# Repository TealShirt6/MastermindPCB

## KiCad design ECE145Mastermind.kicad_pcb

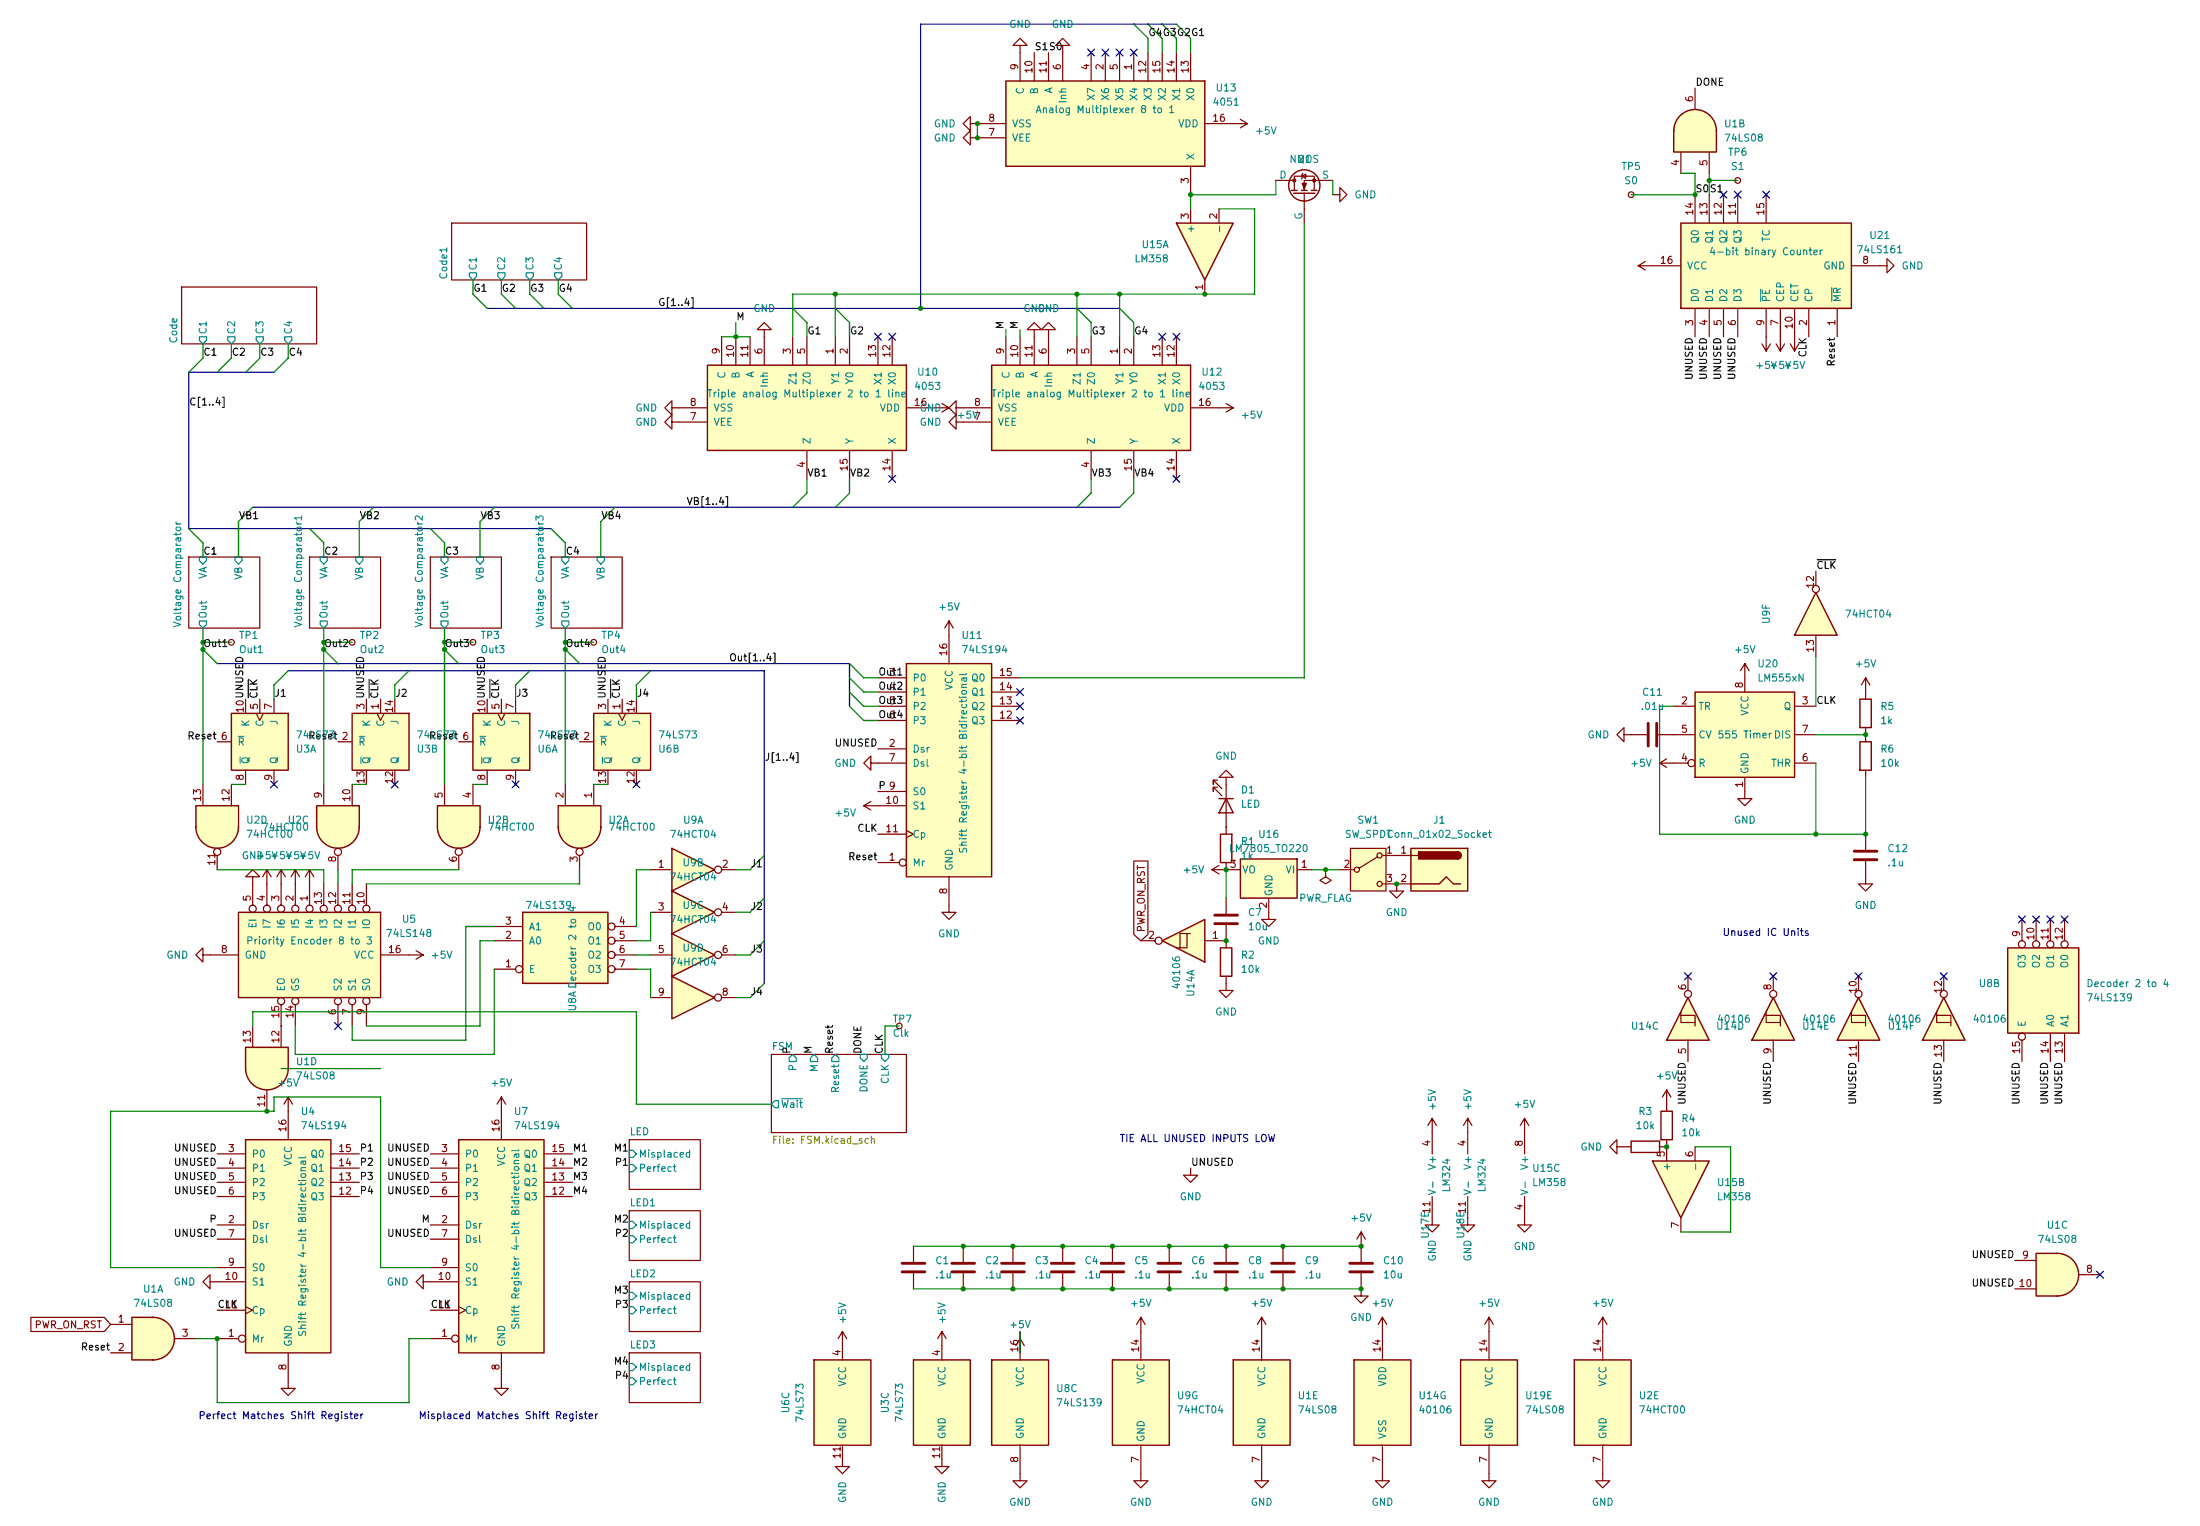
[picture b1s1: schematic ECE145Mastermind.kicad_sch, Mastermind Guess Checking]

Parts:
C1, C2, C3, C4, C5, C6, C8, C9, C12: .1u; C_0805_2012Metric_Pad1.18x1.45mm_HandSolder
C7, C10: 10u; C_0805_2012Metric_Pad1.18x1.45mm_HandSolder
C11: .01u; C_0805_2012Metric_Pad1.18x1.45mm_HandSolder
D1: LED; LED_0805_2012Metric_Pad1.15x1.40mm_HandSolder
J1: Conn_01x02_Socket; BarrelJack_Horizontal
Q1: NMOS; TO-220-3_Horizontal_TabDown
R1, R5: 1k; R_0805_2012Metric_Pad1.20x1.40mm_HandSolder
R2, R3, R4, R6: 10k; R_0805_2012Metric_Pad1.20x1.40mm_HandSolder
SW1: SW_SPDT; SW_Slide_SPDT_Straight_CK_OS102011MS2Q
TP1: Out1; TestPoint_Pad_1.5x1.5mm
TP2: Out2; TestPoint_Pad_1.5x1.5mm
TP3: Out3; TestPoint_Pad_1.5x1.5mm
TP4: Out4; TestPoint_Pad_1.5x1.5mm
TP5: S0; TestPoint_Pad_1.5x1.5mm
TP6: S1; TestPoint_Pad_1.5x1.5mm
TP7: Clk; TestPoint_Pad_1.5x1.5mm
U1, U19: 74LS08; SOIC-14_3.9x8.7mm_P1.27mm
U2: 74HCT00; SOIC-14_3.9x8.7mm_P1.27mm
U3, U6: 74LS73; SOIC-14_3.9x8.7mm_P1.27mm
U4, U7, U11: 74LS194; SOIC-16_3.9x9.9mm_P1.27mm
U5: 74LS148; SOIC-16_3.9x9.9mm_P1.27mm
U8: 74LS139; SOIC-16_3.9x9.9mm_P1.27mm
U9: 74HCT04; SOIC-14_3.9x8.7mm_P1.27mm
U10, U12: 4053; SOIC-16_3.9x9.9mm_P1.27mm
U13: 4051; SOIC-16_3.9x9.9mm_P1.27mm
U14: 40106; SOIC-14_3.9x8.7mm_P1.27mm
U15: LM358; SOIC-8_3.9x4.9mm_P1.27mm
U16: LM7805_TO220; TO-220-3_Horizontal_TabDown
U17, U18: LM324; SOIC-14_3.9x8.7mm_P1.27mm
U20: LM555xN; SOIC-8_3.9x4.9mm_P1.27mm
U21: 74LS161; SOIC-16_3.9x9.9mm_P1.27mm

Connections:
+5V: C1.1, C2.1, C3.1, C4.1, C5.1, C6.1, C7.1, C8.1, C9.1, C10.1, R1.1, R4.1, R5.1, U1.14 (VCC), U2.14 (VCC), U3.4 (VCC), U4.16 (VCC), U5.1 (I4), U5.2 (I5), U5.3 (I6), U5.4 (I7), U5.16 (VCC), U6.4 (VCC), U7.16 (VCC), U8.16 (VCC), U9.14 (VCC), U10.16 (VDD), U11.10 (S1), U11.16 (VCC), U12.16 (VDD), U13.16 (VDD), U14.14 (VDD), U15.8 (V+), U16.3 (VO), U17.4 (V+), U18.4 (V+), U19.14 (VCC), U20.4 (R), U20.8 (VCC), U21.7 (CEP), U21.9 (~PE), U21.10 (CET), U21.16 (VCC); also elsewhere on the board
/CLK: TP7.1 (1_1), U4.11 (Cp), U7.11 (Cp), U9.13, U11.11 (Cp), U20.3 (Q), U21.2 (CP); also elsewhere on the board
/DONE: U1.6; also elsewhere on the board
/FSM/~Wait: U1.13; also elsewhere on the board
/G1: U10.5 (Z0), U13.13 (X0); also elsewhere on the board
/G2: U10.2 (Y0), U13.14 (X1); also elsewhere on the board
/G3: U12.5 (Z0), U13.15 (X2); also elsewhere on the board
/G4: U12.2 (Y0), U13.12 (X3); also elsewhere on the board
/J1: U3.7 (J), U9.2
/J2: U3.14 (J), U9.4
/J3: U6.7 (J), U9.6
/J4: U6.14 (J), U9.8
/M: U7.2 (Dsr), U10.9 (C), U10.10 (B), U10.11 (A), U12.9 (C), U12.10 (B); also elsewhere on the board
/M1: U7.15 (Q0); also elsewhere on the board
/M2: U7.14 (Q1); also elsewhere on the board
/M3: U7.13 (Q2); also elsewhere on the board
/M4: U7.12 (Q3); also elsewhere on the board
/Out1: TP1.1 (1_1), U2.13, U11.3 (P0); also elsewhere on the board
/Out2: TP2.1 (1_1), U2.9, U11.4 (P1); also elsewhere on the board
/Out3: TP3.1 (1_1), U2.5, U11.5 (P2); also elsewhere on the board
/Out4: TP4.1 (1_1), U2.2, U11.6 (P3); also elsewhere on the board
/P: U4.2 (Dsr), U11.9 (S0); also elsewhere on the board
/P1: U4.15 (Q0); also elsewhere on the board
/P2: U4.14 (Q1); also elsewhere on the board
/P3: U4.13 (Q2); also elsewhere on the board
/P4: U4.12 (Q3); also elsewhere on the board
/Reset: U1.2, U3.2 (~R), U3.6 (~R), U6.2 (~R), U6.6 (~R), U11.1 (Mr), U21.1 (~MR); also elsewhere on the board
/S0: TP5.1 (1_1), U1.4, U13.11 (A), U21.14 (Q0)
/S1: TP6.1 (1_1), U1.5, U13.10 (B), U21.13 (Q1)
/VB1: U10.4 (Z); also elsewhere on the board
/VB2: U10.15 (Y); also elsewhere on the board
/VB3: U12.4 (Z); also elsewhere on the board
/VB4: U12.15 (Y); also elsewhere on the board
/~CLK: U3.1 (C), U3.5 (C), U6.1 (C), U6.5 (C), U9.12
GND: C1.2, C2.2, C3.2, C4.2, C5.2, C6.2, C8.2, C9.2, C10.2, C11.2, C12.2, D1.1 (K), J1.2, Q1.3 (S), R2.2, R3.1, SW1.3 (C), U1.7 (GND), U1.9, U1.10, U2.7 (GND), U3.3 (K), U3.10 (K), U3.11 (GND), U4.3 (P0), U4.4 (P1), U4.5 (P2), U4.6 (P3), U4.7 (Dsl), U4.8 (GND), U4.10 (S1), U5.5 (EI), U5.8 (GND), U6.3 (K), U6.10 (K), U6.11 (GND), U7.3 (P0), U7.4 (P1), U7.5 (P2), U7.6 (P3), U7.7 (Dsl), U7.8 (GND), U7.10 (S1), U8.8 (GND), U8.13 (A1), U8.14 (A0), U8.15 (E), U9.7 (GND), U10.6 (Inh), U10.7 (VEE), U10.8 (VSS), U11.2 (Dsr), U11.7 (Dsl), U11.8 (GND), U12.6 (Inh), U12.7 (VEE), U12.8 (VSS), U12.11 (A), U13.6 (Inh), U13.7 (VEE), U13.8 (VSS), U13.9 (C), U14.5, U14.7 (VSS), U14.9, U14.11, U14.13, U15.4 (V-), U16.2 (GND), U17.11 (V-), U18.11 (V-), U19.7 (GND), U20.1 (GND), U21.3 (D0), U21.4 (D1), U21.5 (D2), U21.6 (D3), U21.8 (GND); also elsewhere on the board
unnamed: C7.2, R2.1, U14.1
unnamed: D1.2 (A), R1.2
unnamed: Q1.2 (D), U13.3 (X), U15.3 (+)
unnamed: Q1.1 (G), U11.15 (Q0)
unnamed: J1.1, SW1.1 (A)
unnamed: SW1.2 (B), U16.1 (VI)
unnamed: U2.12, U3.8 (~Q)
unnamed: U2.10, U3.13 (~Q)
unnamed: U1.3, U4.1 (Mr), U7.1 (Mr)
unnamed: U1.11, U4.9 (S0), U7.9 (S0)
unnamed: U1.12, U5.15 (EO)
unnamed: U5.14 (GS), U8.1 (E)
unnamed: U2.6, U5.11 (I1)
unnamed: U2.8, U5.12 (I2)
unnamed: U2.11, U5.13 (I3)
unnamed: U2.3, U5.10 (IO)
unnamed: U5.9 (S0), U8.2 (A0)
unnamed: U5.7 (S1), U8.3 (A1)
unnamed: U2.4, U6.8 (~Q)
unnamed: U2.1, U6.13 (~Q)
unnamed: U8.4 (O0), U9.1
unnamed: U8.5 (O1), U9.3
unnamed: U8.6 (O2), U9.5
unnamed: U8.7 (O3), U9.9
unnamed: U10.1 (Y1), U10.3 (Z1), U12.1 (Y1), U12.3 (Z1), U15.1, U15.2 (-)
unnamed: R3.2, R4.2, U15.5 (+)
unnamed: U15.6 (-), U15.7
unnamed: C11.1, U20.5 (CV)
unnamed: R5.2, R6.1, U20.7 (DIS)
unnamed: C12.1, R6.2, U20.2 (TR), U20.6 (THR)
PWR_ON_RST: U1.1, U14.2; also elsewhere on the board

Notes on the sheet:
Misplaced Matches Shift Register
Perfect Matches Shift Register
Unused IC Units
TIE ALL UNUSED INPUTS LOW

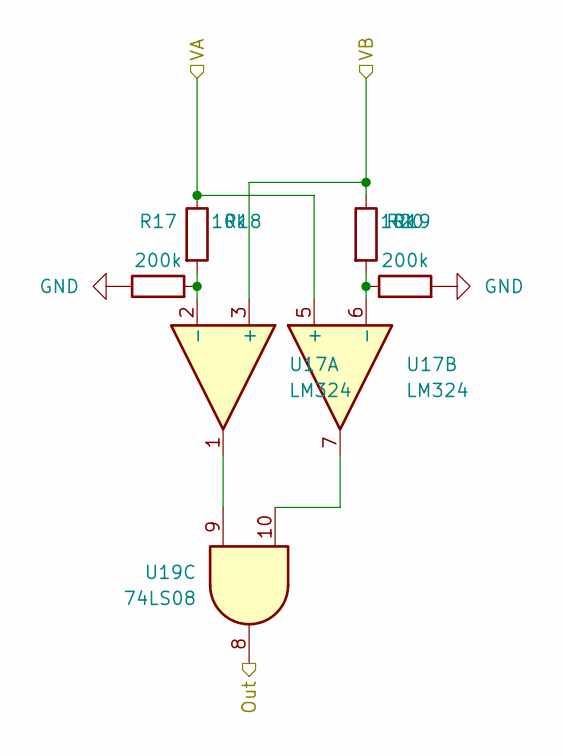
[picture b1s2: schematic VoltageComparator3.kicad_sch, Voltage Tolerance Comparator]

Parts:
R17, R20: 200k; R_0805_2012Metric_Pad1.20x1.40mm_HandSolder
R18, R19: 10k; R_0805_2012Metric_Pad1.20x1.40mm_HandSolder
U17: LM324; SOIC-14_3.9x8.7mm_P1.27mm
U19: 74LS08; SOIC-14_3.9x8.7mm_P1.27mm

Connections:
/C3: R18.1, U17.5 (+); also elsewhere on the board
/Out3: U19.8; also elsewhere on the board
/VB3: R19.1, U17.3 (+); also elsewhere on the board
GND: R17.1, R20.2; also elsewhere on the board
unnamed: U17.1, U19.9
unnamed: U17.7, U19.10
unnamed: R17.2, R18.2, U17.2 (-)
unnamed: R19.2, R20.1, U17.6 (-)

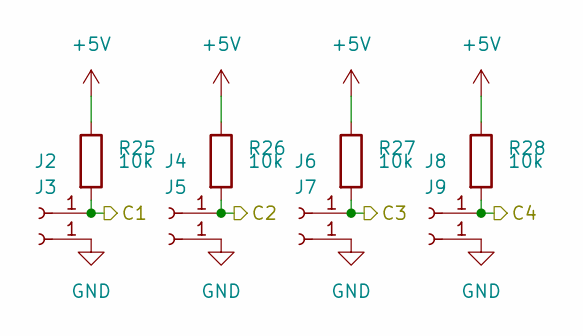
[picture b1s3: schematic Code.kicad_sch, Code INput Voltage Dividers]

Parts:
J2, J3, J4, J5, J6, J7, J8, J9: Conn_01x01_Socket; PinSocket_1x01_P2.54mm_Vertical
R25, R26, R27, R28: 10k; R_0805_2012Metric_Pad1.20x1.40mm_HandSolder

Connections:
+5V: R25.1, R26.1, R27.1, R28.1; also elsewhere on the board
/C1: J2.1 (Pin_1_1), R25.2; also elsewhere on the board
/C2: J4.1 (Pin_1_1), R26.2; also elsewhere on the board
/C3: J6.1 (Pin_1_1), R27.2; also elsewhere on the board
/C4: J8.1 (Pin_1_1), R28.2; also elsewhere on the board
GND: J3.1 (Pin_1_1), J5.1 (Pin_1_1), J7.1 (Pin_1_1), J9.1 (Pin_1_1); also elsewhere on the board

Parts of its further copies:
J10, J11, J12, J13, J14, J15, J16, J17: Conn_01x01_Socket; PinSocket_1x01_P2.54mm_Vertical
R29, R30, R31, R32: 10k; R_0805_2012Metric_Pad1.20x1.40mm_HandSolder

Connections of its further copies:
+5V: R29.1, R30.1, R31.1, R32.1; also elsewhere on the board
/G1: J10.1 (Pin_1_1), R29.2; also elsewhere on the board
/G2: J12.1 (Pin_1_1), R30.2; also elsewhere on the board
/G3: J14.1 (Pin_1_1), R31.2; also elsewhere on the board
/G4: J16.1 (Pin_1_1), R32.2; also elsewhere on the board
GND: J11.1 (Pin_1_1), J13.1 (Pin_1_1), J15.1 (Pin_1_1), J17.1 (Pin_1_1); also elsewhere on the board

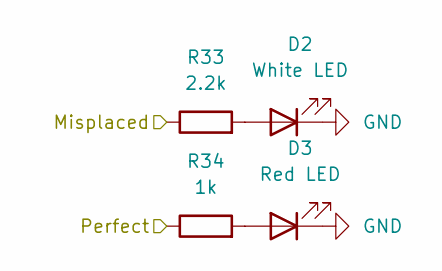
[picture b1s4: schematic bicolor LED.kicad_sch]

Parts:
D2: White LED; LED_0603_1608Metric_Pad1.05x0.95mm_HandSolder
D3: Red LED; LED_0603_1608Metric_Pad1.05x0.95mm_HandSolder
R33: 2.2k; R_0805_2012Metric_Pad1.20x1.40mm_HandSolder
R34: 1k; R_0805_2012Metric_Pad1.20x1.40mm_HandSolder

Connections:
/M2: R33.1; also elsewhere on the board
/P2: R34.1; also elsewhere on the board
GND: D2.1 (K), D3.1 (K); also elsewhere on the board
unnamed: D2.2 (A), R33.2
unnamed: D3.2 (A), R34.2

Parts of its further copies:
D4, D6, D8: White LED; LED_0603_1608Metric_Pad1.05x0.95mm_HandSolder
D5, D7, D9: Red LED; LED_0603_1608Metric_Pad1.05x0.95mm_HandSolder
R35, R37, R39: 2.2k; R_0805_2012Metric_Pad1.20x1.40mm_HandSolder
R36, R38, R40: 1k; R_0805_2012Metric_Pad1.20x1.40mm_HandSolder

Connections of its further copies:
/M1: R37.1; also elsewhere on the board
/M3: R35.1; also elsewhere on the board
/M4: R39.1; also elsewhere on the board
/P1: R38.1; also elsewhere on the board
/P3: R36.1; also elsewhere on the board
/P4: R40.1; also elsewhere on the board
GND: D4.1 (K), D5.1 (K), D6.1 (K), D7.1 (K), D8.1 (K), D9.1 (K); also elsewhere on the board
unnamed: D4.2 (A), R35.2
unnamed: D5.2 (A), R36.2
unnamed: D6.2 (A), R37.2
unnamed: D7.2 (A), R38.2
unnamed: D8.2 (A), R39.2
unnamed: D9.2 (A), R40.2

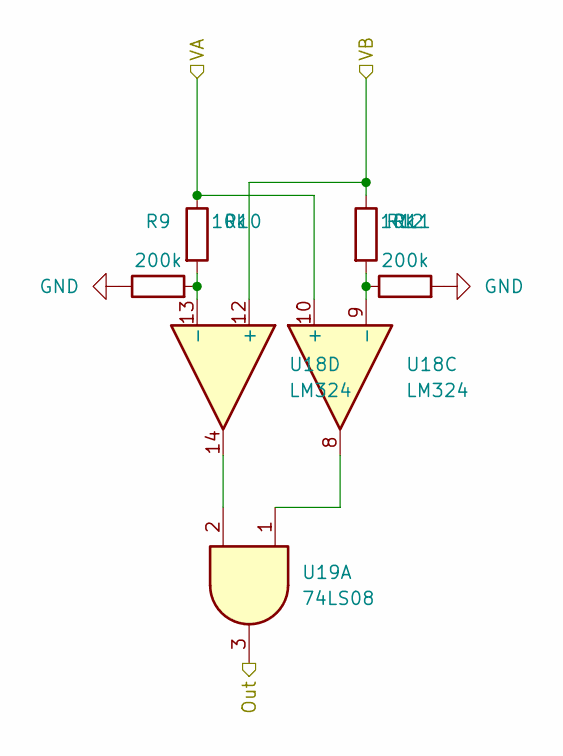
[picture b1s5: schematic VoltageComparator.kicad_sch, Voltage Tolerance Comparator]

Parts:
R9, R12: 200k; R_0805_2012Metric_Pad1.20x1.40mm_HandSolder
R10, R11: 10k; R_0805_2012Metric_Pad1.20x1.40mm_HandSolder
U18: LM324; SOIC-14_3.9x8.7mm_P1.27mm
U19: 74LS08; SOIC-14_3.9x8.7mm_P1.27mm

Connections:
/C1: R10.1, U18.10 (+); also elsewhere on the board
/Out1: U19.3; also elsewhere on the board
/VB1: R11.1, U18.12 (+); also elsewhere on the board
GND: R9.1, R12.2; also elsewhere on the board
unnamed: U18.8, U19.1
unnamed: U18.14, U19.2
unnamed: R11.2, R12.1, U18.9 (-)
unnamed: R9.2, R10.2, U18.13 (-)

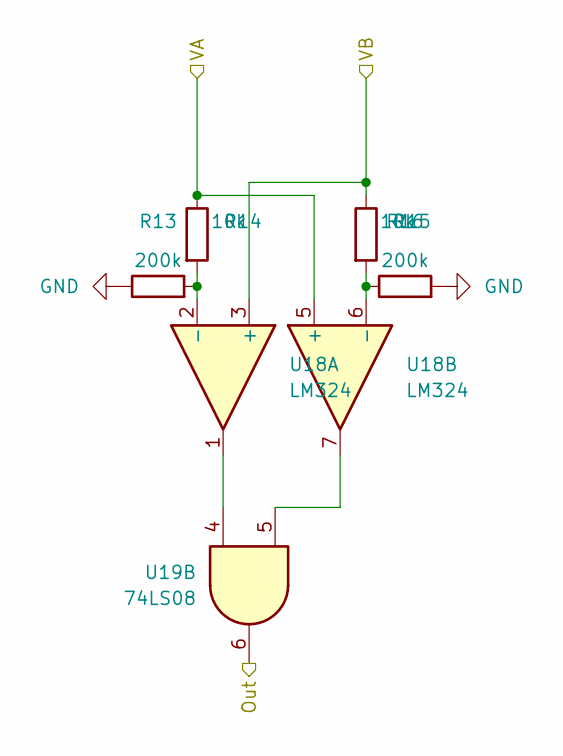
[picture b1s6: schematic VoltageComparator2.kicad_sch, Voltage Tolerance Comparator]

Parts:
R13, R16: 200k; R_0805_2012Metric_Pad1.20x1.40mm_HandSolder
R14, R15: 10k; R_0805_2012Metric_Pad1.20x1.40mm_HandSolder
U18: LM324; SOIC-14_3.9x8.7mm_P1.27mm
U19: 74LS08; SOIC-14_3.9x8.7mm_P1.27mm

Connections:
/C2: R14.1, U18.5 (+); also elsewhere on the board
/Out2: U19.6; also elsewhere on the board
/VB2: R15.1, U18.3 (+); also elsewhere on the board
GND: R13.1, R16.2; also elsewhere on the board
unnamed: U18.1, U19.4
unnamed: U18.7, U19.5
unnamed: R13.2, R14.2, U18.2 (-)
unnamed: R15.2, R16.1, U18.6 (-)

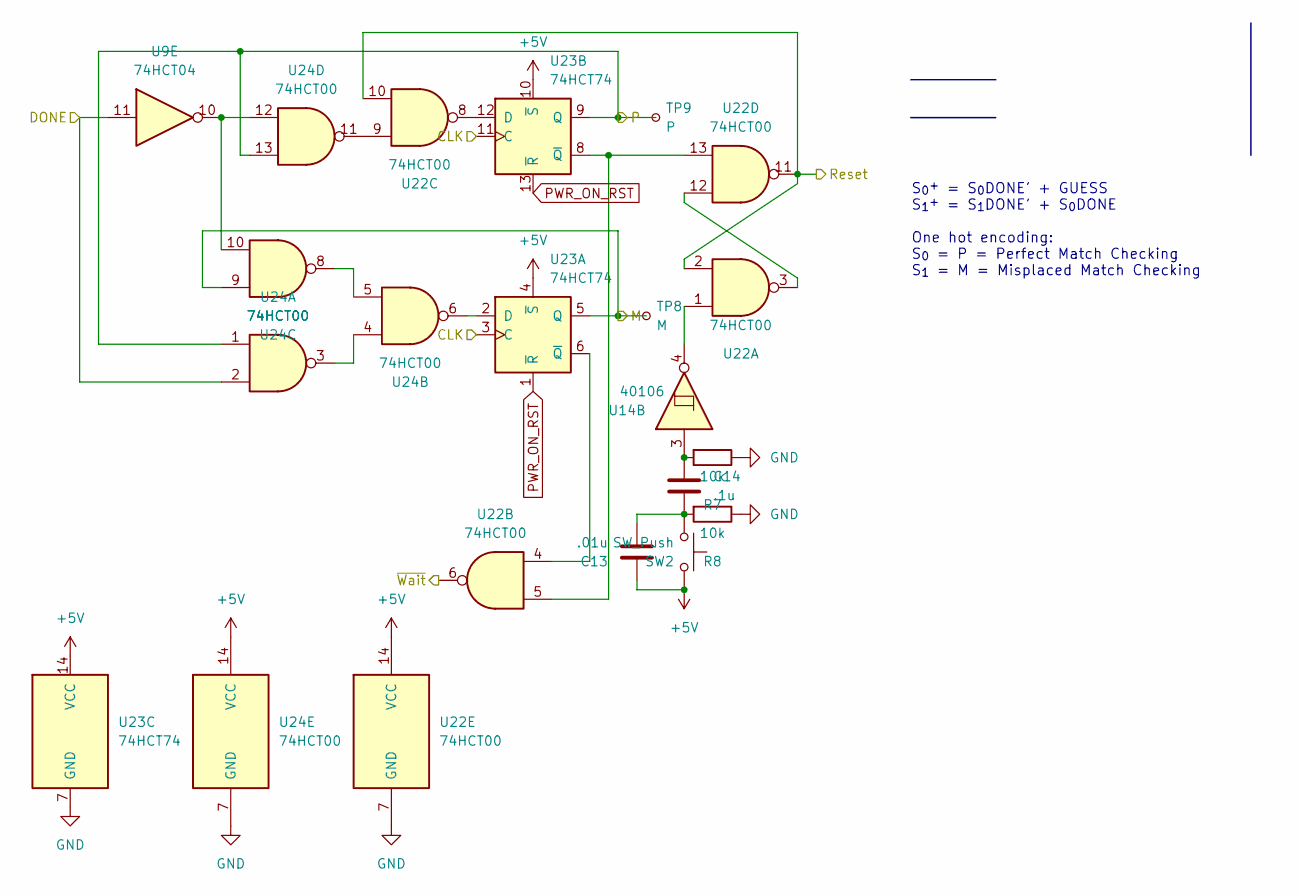
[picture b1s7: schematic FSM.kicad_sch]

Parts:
C13: .01u; C_0805_2012Metric_Pad1.18x1.45mm_HandSolder
C14: .1u; C_0805_2012Metric_Pad1.18x1.45mm_HandSolder
R7, R8: 10k; R_0805_2012Metric_Pad1.20x1.40mm_HandSolder
SW2: SW_Push; SW_SPST_Omron_B3F-40xx
TP8: M; TestPoint_Pad_1.5x1.5mm
TP9: P; TestPoint_Pad_1.5x1.5mm
U9: 74HCT04; SOIC-14_3.9x8.7mm_P1.27mm
U14: 40106; SOIC-14_3.9x8.7mm_P1.27mm
U22, U24: 74HCT00; SOIC-14_3.9x8.7mm_P1.27mm
U23: 74HCT74; SOIC-14_3.9x8.7mm_P1.27mm

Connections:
+5V: C13.1, SW2.2, U22.14 (VCC), U23.4 (~S), U23.10 (~S), U23.14 (VCC), U24.14 (VCC); also elsewhere on the board
/CLK: U23.3 (C), U23.11 (C); also elsewhere on the board
/DONE: U9.11, U24.2; also elsewhere on the board
/FSM/~Wait: U22.6; also elsewhere on the board
/M: TP8.1 (1_1), U23.5 (Q), U24.9; also elsewhere on the board
/P: TP9.1 (1_1), U23.9 (Q), U24.1, U24.13; also elsewhere on the board
/Reset: U22.2, U22.10, U22.11; also elsewhere on the board
GND: R7.1, R8.1, U22.7 (GND), U23.7 (GND), U24.7 (GND); also elsewhere on the board
unnamed: C13.2, C14.1, R8.2, SW2.1
unnamed: C14.2, R7.2, U14.3
unnamed: U14.4, U22.1
unnamed: U22.9, U24.11
unnamed: U22.3, U22.12
unnamed: U23.2 (D), U24.6
unnamed: U22.4, U23.6 (~Q)
unnamed: U22.8, U23.12 (D)
unnamed: U22.5, U22.13, U23.8 (~Q)
unnamed: U24.3, U24.4
unnamed: U24.5, U24.8
unnamed: U9.10, U24.10, U24.12
PWR_ON_RST: U23.1 (~R), U23.13 (~R); also elsewhere on the board

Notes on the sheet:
S_{0}^{+} = S_{0}DONE' + GUESS S_{1}^{+} = S_{1}DONE' + S_{0}DONE One hot encoding: S_{0} = P = Perfect Match Checking S_{1} = M = Misplaced Match Checking

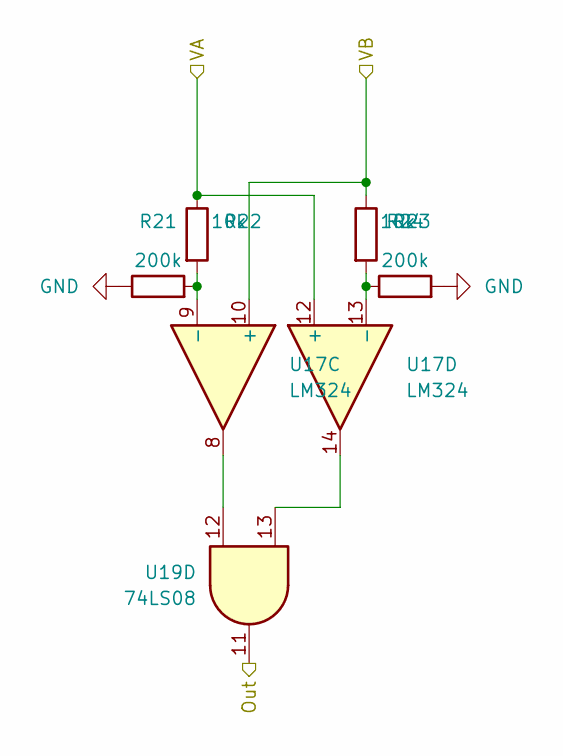
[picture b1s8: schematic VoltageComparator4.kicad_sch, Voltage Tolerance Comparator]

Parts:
R21, R24: 200k; R_0805_2012Metric_Pad1.20x1.40mm_HandSolder
R22, R23: 10k; R_0805_2012Metric_Pad1.20x1.40mm_HandSolder
U17: LM324; SOIC-14_3.9x8.7mm_P1.27mm
U19: 74LS08; SOIC-14_3.9x8.7mm_P1.27mm

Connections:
/C4: R22.1, U17.12 (+); also elsewhere on the board
/Out4: U19.11; also elsewhere on the board
/VB4: R23.1, U17.10 (+); also elsewhere on the board
GND: R21.1, R24.2; also elsewhere on the board
unnamed: U17.8, U19.12
unnamed: U17.14, U19.13
unnamed: R21.2, R22.2, U17.9 (-)
unnamed: R23.2, R24.1, U17.13 (-)

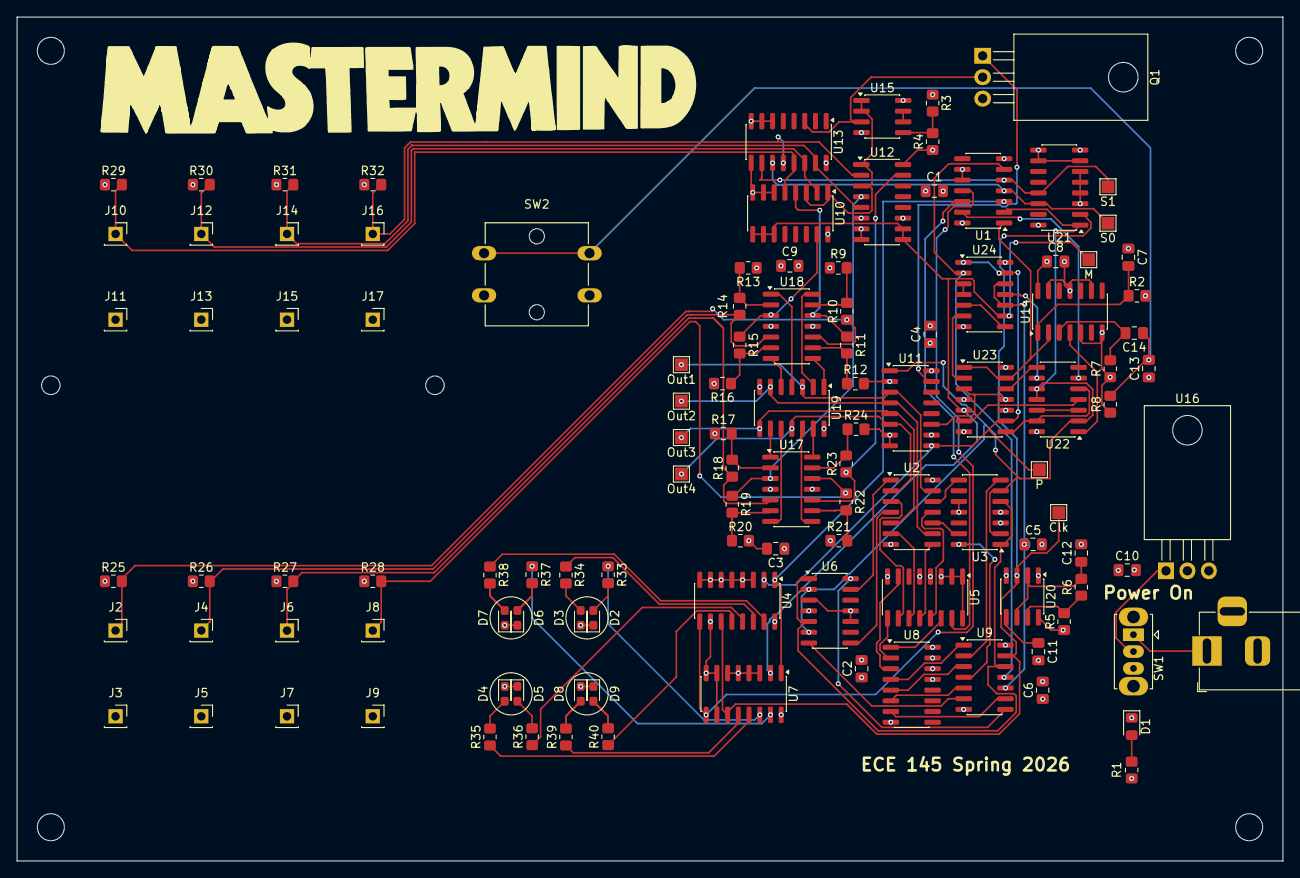
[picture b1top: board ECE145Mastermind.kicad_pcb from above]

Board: 4 copper layers, 150.0 x 100.0 mm, 116 parts (0 on the bottom side), 106 nets.

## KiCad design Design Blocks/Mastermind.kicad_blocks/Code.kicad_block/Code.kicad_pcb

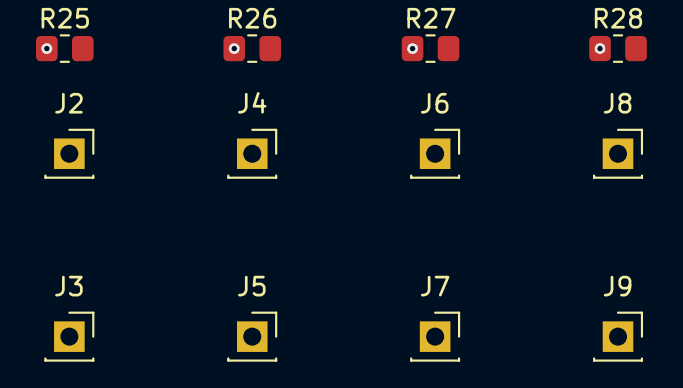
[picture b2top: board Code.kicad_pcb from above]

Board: 4 copper layers, 12 parts (0 on the bottom side), 6 nets, no tracks yet.

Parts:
J2, J3, J4, J5, J6, J7, J8, J9: Conn_01x01_Socket; PinSocket_1x01_P2.54mm_Vertical
R25, R26, R27, R28: 10k; R_0805_2012Metric_Pad1.20x1.40mm_HandSolder

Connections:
+5V: R25.1, R26.1, R27.1, R28.1
/C1: J2.1 (Pin_1_1), R25.2
/C2: J4.1 (Pin_1_1), R26.2
/C3: J6.1 (Pin_1_1), R27.2
/C4: J8.1 (Pin_1_1), R28.2
GND: J3.1 (Pin_1_1), J5.1 (Pin_1_1), J7.1 (Pin_1_1), J9.1 (Pin_1_1)

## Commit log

2026-03-13 Added gitignore
2026-03-14 Added FSM, Button, 555 timer, changed shift registers
2026-03-16 slight tweaks
2026-03-27 Added AND gate for P shift register
2026-04-04 Fixes
2026-04-28 Started PCB Work
2026-04-28 For Sharvesh
2026-04-30 routed
2026-05-01 Ground and Power Plane?
2026-05-01 Finished?
2026-05-02 Final touches
2026-05-02 Updated gitignore
2026-05-03 trying things out
2026-05-08 made things nice
